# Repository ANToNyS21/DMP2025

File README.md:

# DMP2025
sestava na ONSHAPE : https://cad.onshape.com/documents/a55f27827d7d0bf78ad17041/w/e62290534607ad3c1cca5b53/e/726e90d26969cd6e7ac2d84b?renderMode=0&uiState=67c0b942ae4f594e00a113b2

video s funkčností / ukázkou menu:

https://drive.google.com/file/d/1NYgzzBReGRTbW6AwwNUOp2N6VFr0sSx1/view?usp=sharing

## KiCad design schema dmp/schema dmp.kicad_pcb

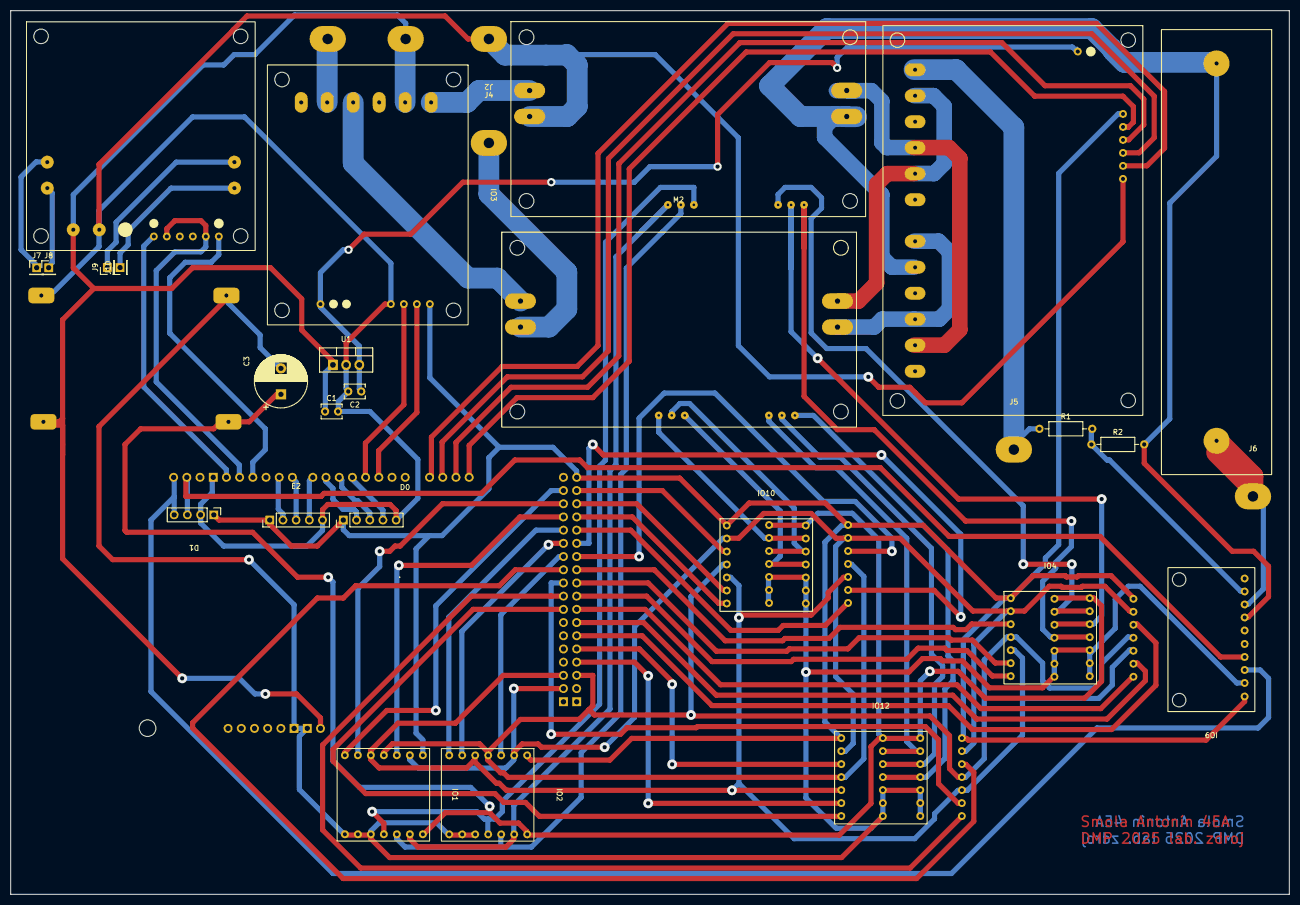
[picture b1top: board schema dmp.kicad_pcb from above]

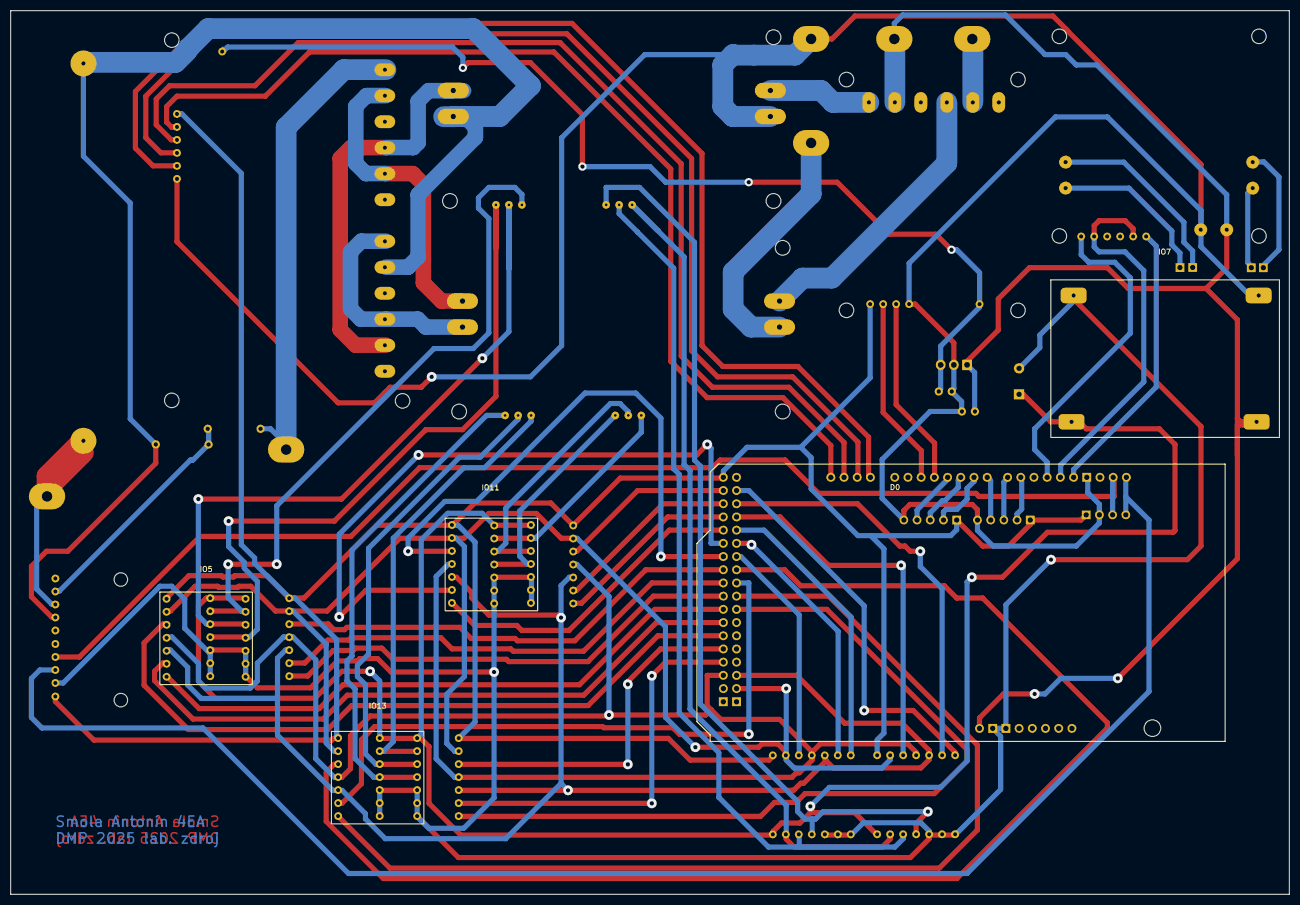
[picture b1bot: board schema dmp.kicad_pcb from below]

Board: 2 copper layers, 246.0 x 170.0 mm, 36 parts (4 on the bottom side), 77 nets.

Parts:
A1: Arduino_Mega2560_R3_Shield; arduino_mega
C1: 0,1 µF; C_Disc_D3.8mm_W2.6mm_P2.50mm
C2: 0,01 µF; C_Disc_D3.8mm_W2.6mm_P2.50mm
C3: 680uF/50V; CP_Radial_D10.0mm_P5.00mm
D1: display
E1: enkoder U; enkoder
E2: enkoder I; enkoder
IO1, IO2, IO10, IO11: MCP41HV51-502E; MCP41HV51
IO3: rele_2x
IO4, IO5, IO12, IO13: MCP41HV51-104E; MCP41HV51
IO7: step_up; step_up_module
IO8: rele_4x
IO9: ADS1115_I2C; ADS1115
IO14: H_mustek
J1: +12v; conn
J2: GND; conn
J3: +12v 2; conn
J4: GND2; conn
J5: out+ regulated; conn
J6: out-; conn
J7: FAN1+; PinHeader_1x01_P2.54mm_Vertical
J8: FAN1-; PinHeader_1x01_P2.54mm_Vertical
J9: FAN2+; PinHeader_1x01_P2.54mm_Vertical
J10: FAN2-; PinHeader_1x01_P2.54mm_Vertical
M1, M2: CC_&_CV_modul
R1: 220k; R_Axial_DIN0207_L6.3mm_D2.5mm_P10.16mm_Horizontal
R2: 17k8; R_Axial_DIN0207_L6.3mm_D2.5mm_P10.16mm_Horizontal
R3: 0.2R; power_rezistor_100w_0.2R
U1: L78S05CV; TO-220-3_Vertical

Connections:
12V+: A1.VIN, C1.1, IO3.22, IO7.1 (VC_+12V), IO14.5 (+12v), J1.1, U1.1 (IN)
+30V digipot: C3.1, IO1.14 (V+30v), IO2.14 (V+30v), IO4.14 (V+30v), IO5.14 (V+30v), IO7.3 (U_OUT), IO10.14 (V+30v), IO11.14 (V+30v), IO12.14 (V+30v), IO13.14 (V+30v)
Arduino_EnA: A1.D13, IO14.7 (ENA)
Arduino_EnB: A1.D11, IO14.8 (ENB)
Arduino_IN2_IN4: A1.D12, IO14.9 (IN1), IO14.12 (IN4)
Arduino_SCL: A1.SCL, D1.4 (SCL), IO9.3 (SCL)
Arduino_SDA: A1.SDA, D1.3 (SDA), IO9.4 (SDA)
Arduino_rele_2x_1: A1.D3 (D3_INT1), IO3.14 (IN1)
Arduino_rele_2x_2: A1.D2 (D2_INT0), IO3.24 (IN2)
Arduino_rele_4x_1: A1.D14 (D14/TX3), IO8.14 (IN1)
Arduino_rele_4x_2: A1.D15 (D15/RX3), IO8.24 (IN2)
Arduino_rele_4x_3: A1.D16 (D16/TX2), IO8.34 (IN3)
Arduino_rele_4x_4: A1.D17 (D17/RX2), IO8.44 (IN4)
CC1: IO10.13 (P0A), IO11.13 (P0A), M2.5 (TRIMR_CC_1)
CC2: IO10.12 (P0W), IO11.12 (P0W), M2.6 (TRIMR_CC_2)
CC3: IO10.11 (P0B), IO11.11 (P0B), M2.7 (TRIMR_CC_3)
CV1: IO12.13 (P0A), IO13.13 (P0A), M2.8 (TRIMR_CV_1)
CV2: IO12.12 (P0W), IO13.12 (P0W), M2.9 (TRIMR_CV_2)
CV3: IO12.11 (P0B), IO13.11 (P0B), M2.10 (TRIMR_CV_3)
GNDD: A1.GND1 (GND), C1.2, C2.2, D1.2 (VCC), E1.5 (GND), E2.5 (GND), IO3.1 (GND), IO7.2 (GND_IN), IO8.1 (GND), IO14.6 (GND), J2.1, M1.2 (IN_GNDD), U1.2 (GND)
JD-VCC: C2.1, IO3.3 (JD-VCC), IO8.3 (JD-VCC), U1.3 (OUT)
MISO_SDO: A1.D50 (D50_MISO), IO1.5 (SDO), IO2.5 (SDO), IO4.5 (SDO), IO5.5 (SDO), IO10.5 (SDO), IO11.5 (SDO), IO12.5 (SDO), IO13.5 (SDO)
MOSI_SDI: A1.D51 (D51_MOSI), IO1.4 (SDI), IO2.4 (SDI), IO4.4 (SDI), IO5.4 (SDI), IO10.4 (SDI), IO11.4 (SDI), IO12.4 (SDI), IO13.4 (SDI)
unnamed: IO1.13 (P0A), IO2.13 (P0A), M1.5 (TRIMR_CC_1)
unnamed: IO1.11 (P0B), IO2.11 (P0B), M1.7 (TRIMR_CC_3)
unnamed: IO1.12 (P0W), IO2.12 (P0W), M1.6 (TRIMR_CC_2)
unnamed: IO4.13 (P0A), IO5.13 (P0A), M1.8 (TRIMR_CV_1)
unnamed: IO4.11 (P0B), IO5.11 (P0B), M1.10 (TRIMR_CV_3)
unnamed: IO4.12 (P0W), IO5.12 (P0W), M1.9 (TRIMR_CV_2)
unnamed: IO8.22, IO9.7 (A0), M1.4 (OUT_GNDD), R2.2, R3.1
unnamed: IO9.8 (A1), J6.1, R3.2
unnamed: IO9.9 (A2), R1.2, R2.1
unnamed: IO14.1 (OUT1), J7.1
unnamed: IO14.2 (OUT2), J8.1
unnamed: IO14.3 (OUT3), J10.1
unnamed: IO14.4 (OUT4), J9.1
unnamed: IO3.12, J3.1
unnamed: J4.1, M2.2 (IN_GNDD)
unnamed: IO8.43, J5.1, R1.1
unnamed: IO3.23, M1.1 (IN_DC_0-30V)
unnamed: IO8.12, IO8.33, M1.3 (OUT_DC_0-30V)
unnamed: IO3.13, M2.1 (IN_DC_0-30V)
unnamed: IO8.32, IO8.42, M2.3 (OUT_DC_0-30V)
unnamed: IO8.13, IO8.23, M2.4 (OUT_GNDD)
arduino 5v: A1.5V4 (5V), D1.1 (GND), E1.1 (5V), E2.1 (5V), IO1.1 (VL_+5v), IO2.1 (VL_+5v), IO3.2 (VCC), IO4.1 (VL_+5v), IO5.1 (VL_+5v), IO8.2 (VCC), IO9.1 (VDD), IO10.1 (VL_+5v), IO11.1 (VL_+5v), IO12.1 (VL_+5v), IO13.1 (VL_+5v)
arduino GND3: A1.GND2 (GND), A1.GND3 (GND), C3.2, IO1.8 (NC), IO1.9 (DGND), IO1.10 (V-), IO2.8 (NC), IO2.9 (DGND), IO2.10 (V-), IO4.8 (NC), IO4.9 (DGND), IO4.10 (V-), IO5.8 (NC), IO5.9 (DGND), IO5.10 (V-), IO7.4 (GND_OUT), IO9.2 (GND), IO10.8 (NC), IO10.9 (DGND), IO10.10 (V-), IO11.8 (NC), IO11.9 (DGND), IO11.10 (V-), IO12.8 (NC), IO12.9 (DGND), IO12.10 (V-), IO13.8 (NC), IO13.9 (DGND), IO13.10 (V-)
arduino sck: A1.D52 (D52_SCK), IO1.2 (SCK), IO2.2 (SCK), IO4.2 (SCK), IO5.2 (SCK), IO10.2 (SCK), IO11.2 (SCK), IO12.2 (SCK), IO13.2 (SCK)
arduino_CS_1: A1.D26, IO1.3 (CS)
arduino_CS_2: A1.D32, IO2.3 (CS)
arduino_CS_3: A1.D35, IO4.3 (CS)
arduino_CS_4: A1.D45, IO5.3 (CS)
arduino_CS_5: A1.D23, IO10.3 (CS)
arduino_CS_6: A1.D33, IO11.3 (CS)
arduino_CS_7: A1.D47, IO12.3 (CS)
arduino_CS_8: A1.D34, IO13.3 (CS)
arduino_SHDN_1: A1.D22, IO1.7 (SHDN)
arduino_SHDN_2: A1.D28, IO2.7 (SHDN)
arduino_SHDN_3: A1.D39, IO4.7 (SHDN)
arduino_SHDN_4: A1.D41, IO5.7 (SHDN)
arduino_SHDN_5: A1.D27, IO10.7 (SHDN)
arduino_SHDN_6: A1.D29, IO11.7 (SHDN)
arduino_SHDN_7: A1.D40, IO12.7 (SHDN)
arduino_SHDN_8: A1.D38, IO13.7 (SHDN)
arduino_WLAT_1: A1.D24, IO1.6 (WLAT)
arduino_WLAT_2: A1.D30, IO2.6 (WLAT)
arduino_WLAT_3: A1.D37, IO4.6 (WLAT)
arduino_WLAT_4: A1.D43, IO5.6 (WLAT)
arduino_WLAT_5: A1.D25, IO10.6 (WLAT)
arduino_WLAT_6: A1.D31, IO11.6 (WLAT)
arduino_WLAT_7: A1.D49, IO12.6 (WLAT)
arduino_WLAT_8: A1.D36, IO13.6 (WLAT)
enkoder I KEY: A1.D9, E2.2 (KEY)
enkoder I S1: A1.D7, E2.4 (S1)
enkoder I S2: A1.D8, E2.3 (S2)
enkoder U KEY: A1.D6, E1.2 (KEY)
enkoder U S1: A1.D4, E1.4 (S1)
enkoder U S2: A1.D5, E1.3 (S2)

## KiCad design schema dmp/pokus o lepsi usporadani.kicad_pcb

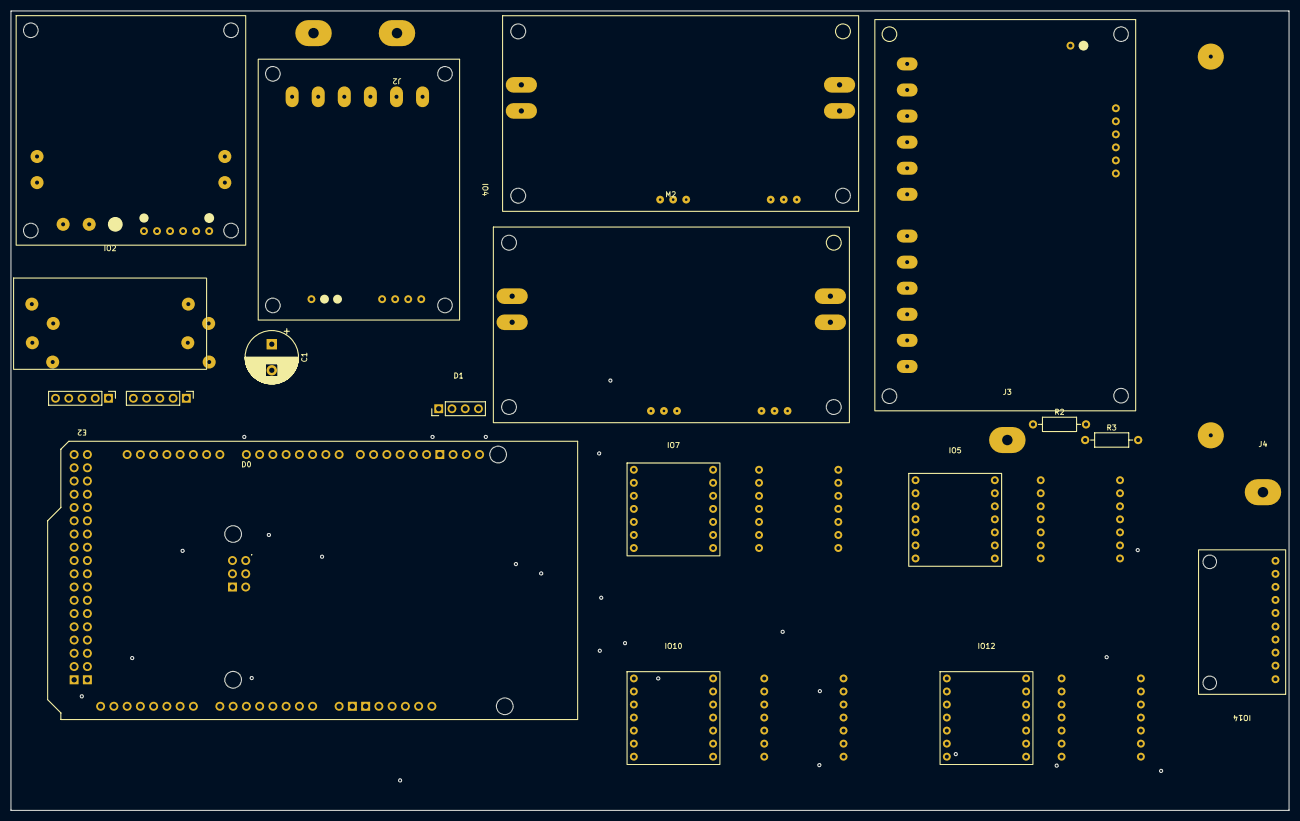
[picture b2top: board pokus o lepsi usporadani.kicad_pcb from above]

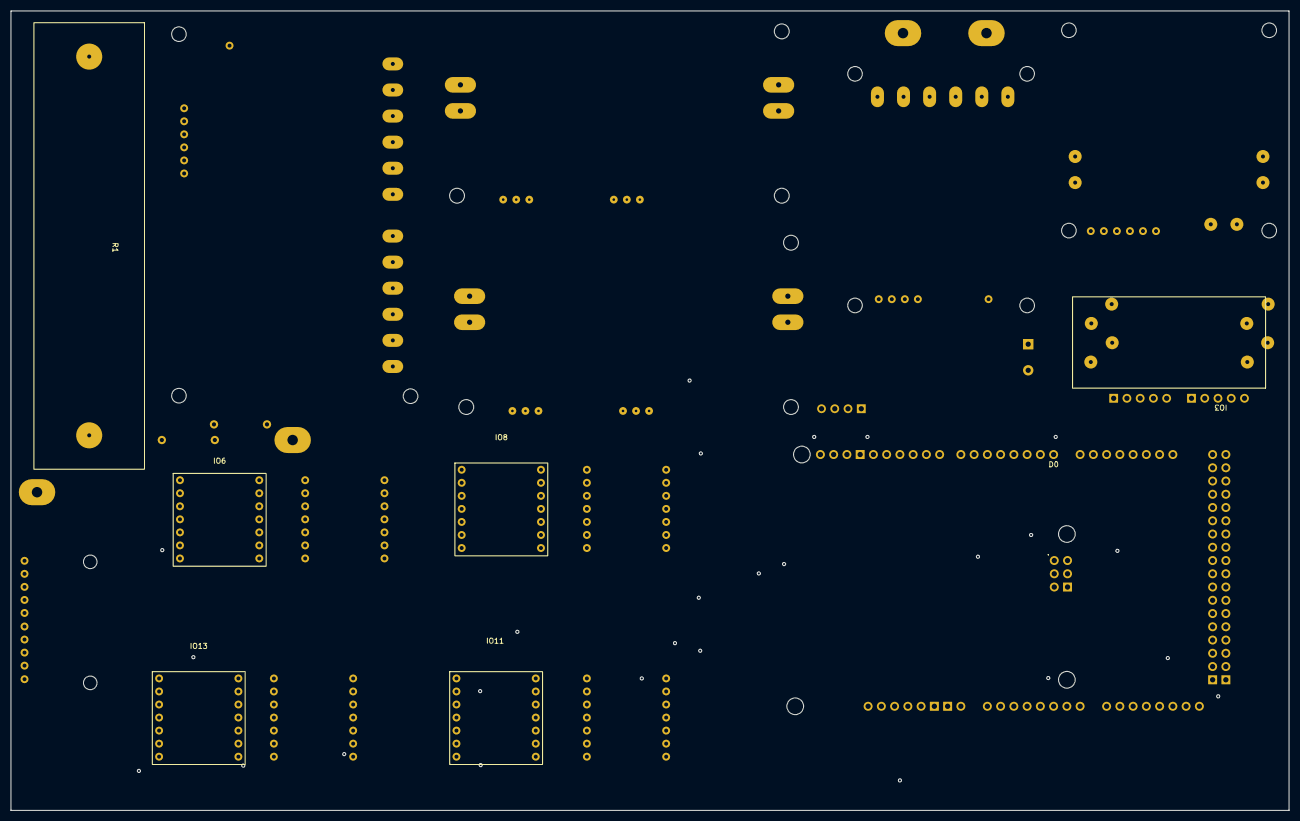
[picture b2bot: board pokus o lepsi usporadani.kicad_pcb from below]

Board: 2 copper layers, 245.0 x 153.2 mm, 28 parts (7 on the bottom side), 71 nets, no tracks yet.

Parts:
A1: Arduino_Mega2560_R3_Shield; arduino_mega
C1: 680uF/50V; CP_Radial_D10.0mm_P5.00mm
D1: display
E1: enkoder U; enkoder
E2: enkoder I; enkoder
IO1: H_mustek
IO2, IO3: step_up_28V
IO4: rele_2x
IO5, IO6, IO10, IO11: MCP41HV51-104E; MCP41HV51
IO7, IO8, IO12, IO13: MCP41HV51-502E; MCP41HV51
IO9: rele_4x
IO14: ADS1115_I2C; ADS1115
J1: +12v; conn
J2: GND; conn
J3: out+ regulated; conn
J4: out-; conn
M1, M2: CC_&_CV_modul
R1: 0.2R; power_rezistor_100w_0.2R
R2: 220k; R_Axial_DIN0207_L6.3mm_D2.5mm_P10.16mm_Horizontal
R3: 17k8; R_Axial_DIN0207_L6.3mm_D2.5mm_P10.16mm_Horizontal

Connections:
12V+: IO1.5 (+12v), IO2.1 (VC_+12V), IO3.1 (VC_+12V), IO4.12, IO4.22, J1.1
+30V digipot: C1.1, IO2.3 (28V_OUT), IO5.14 (V+30v), IO6.14 (V+30v), IO7.14 (V+30v), IO8.14 (V+30v), IO10.14 (V+30v), IO11.14 (V+30v), IO12.14 (V+30v), IO13.14 (V+30v)
Arduino_EnA: A1.D8, IO1.7 (ENA)
Arduino_IN1: A1.D9, IO1.9 (IN1)
Arduino_IN2: A1.D10, IO1.10 (IN2)
Arduino_SCL: A1.SCL, D1.4 (SCL), IO14.4 (SDA)
Arduino_SDA: A1.SDA, D1.3 (SDA), IO14.3 (SCL)
Arduino_rele_2x_1: A1.D2 (D2_INT0), IO4.14 (IN1)
Arduino_rele_2x_2: A1.D3 (D3_INT1), IO4.24 (IN2)
Arduino_rele_4x_1: A1.D4, IO9.14 (IN1)
Arduino_rele_4x_2: A1.D5, IO9.24 (IN2)
Arduino_rele_4x_3: A1.D6, IO9.34 (IN3)
Arduino_rele_4x_4: A1.D7, IO9.44 (IN4)
GNDD: A1.GND1 (GND), D1.2 (VCC), E1.5 (GND), E2.5 (GND), IO1.6 (GND), IO2.2 (GND_IN), IO3.2 (GND_IN), IO4.1 (GND), IO9.1 (GND), J2.1, M1.2 (IN_GNDD), M2.2 (IN_GNDD)
MISO_SDO: A1.D50 (D50_MISO), IO5.5 (SDO), IO6.5 (SDO), IO7.5 (SDO), IO8.5 (SDO), IO10.5 (SDO), IO11.5 (SDO), IO12.5 (SDO), IO13.5 (SDO)
MOSI_SDI: A1.D51 (D51_MOSI), IO5.4 (SDI), IO6.4 (SDI), IO7.4 (SDI), IO8.4 (SDI), IO10.4 (SDI), IO11.4 (SDI), IO12.4 (SDI), IO13.4 (SDI)
unnamed: A1.D24, E1.2 (KEY)
unnamed: A1.D23, E1.4 (S1)
unnamed: A1.D22, E1.3 (S2)
unnamed: A1.D27, E2.2 (KEY)
unnamed: A1.D26, E2.4 (S1)
unnamed: A1.D25, E2.3 (S2)
unnamed: IO2.4 (GND_OUT), IO3.3 (28V_OUT)
unnamed: IO5.13 (P0A), IO6.13 (P0A), M1.10 (TRIMR_CV_3)
unnamed: IO5.11 (P0B), IO6.11 (P0B), M1.8 (TRIMR_CV_1)
unnamed: IO5.12 (P0W), IO6.12 (P0W), M1.9 (TRIMR_CV_2)
unnamed: IO7.13 (P0A), IO8.13 (P0A), M1.5 (TRIMR_CC_1)
unnamed: IO7.11 (P0B), IO8.11 (P0B), M1.7 (TRIMR_CC_3)
unnamed: IO7.12 (P0W), IO8.12 (P0W), M1.6 (TRIMR_CC_2)
unnamed: IO10.13 (P0A), IO11.13 (P0A), M2.10 (TRIMR_CV_3)
unnamed: IO10.11 (P0B), IO11.11 (P0B), M2.8 (TRIMR_CV_1)
unnamed: IO10.12 (P0W), IO11.12 (P0W), M2.9 (TRIMR_CV_2)
unnamed: IO12.13 (P0A), IO13.13 (P0A), M2.5 (TRIMR_CC_1)
unnamed: IO12.11 (P0B), IO13.11 (P0B), M2.7 (TRIMR_CC_3)
unnamed: IO12.12 (P0W), IO13.12 (P0W), M2.6 (TRIMR_CC_2)
unnamed: IO9.22, IO14.7 (A0), M1.4 (OUT_GNDD), R1.1, R3.2
unnamed: IO14.8 (A1), J4.1, R1.2
unnamed: IO14.9 (A2), R2.2, R3.1
unnamed: IO9.43, J3.1, R2.1
unnamed: IO4.23, M1.1 (IN_DC_0-30V)
unnamed: IO9.12, IO9.33, M1.3 (OUT_DC_0-30V)
unnamed: IO4.13, M2.1 (IN_DC_0-30V)
unnamed: IO9.32, IO9.42, M2.3 (OUT_DC_0-30V)
unnamed: IO9.13, IO9.23, M2.4 (OUT_GNDD)
arduino 5v: A1.5V4 (5V), D1.1 (GND), E1.1 (5V), E2.1 (5V), IO4.2 (VCC), IO5.1 (VL_+5v), IO6.1 (VL_+5v), IO7.1 (VL_+5v), IO8.1 (VL_+5v), IO9.2 (VCC), IO10.1 (VL_+5v), IO11.1 (VL_+5v), IO12.1 (VL_+5v), IO13.1 (VL_+5v), IO14.1 (VDD)
arduino GND3: A1.GND2 (GND), A1.GND3 (GND), C1.2, IO3.4 (GND_OUT), IO5.8 (NC), IO5.9 (DGND), IO5.10 (V-), IO6.8 (NC), IO6.9 (DGND), IO6.10 (V-), IO7.8 (NC), IO7.9 (DGND), IO7.10 (V-), IO8.8 (NC), IO8.9 (DGND), IO8.10 (V-), IO10.8 (NC), IO10.9 (DGND), IO10.10 (V-), IO11.8 (NC), IO11.9 (DGND), IO11.10 (V-), IO12.8 (NC), IO12.9 (DGND), IO12.10 (V-), IO13.8 (NC), IO13.9 (DGND), IO13.10 (V-), IO14.2 (GND)
arduino sck: A1.D52 (D52_SCK), IO5.2 (SCK), IO6.2 (SCK), IO7.2 (SCK), IO8.2 (SCK), IO10.2 (SCK), IO11.2 (SCK), IO12.2 (SCK), IO13.2 (SCK)
arduino_CS_1: A1.D19 (D19/RX1), IO7.3 (CS)
arduino_CS_2: A1.D16 (D16/TX2), IO8.3 (CS)
arduino_CS_3: A1.D11, IO5.3 (CS)
arduino_CS_4: A1.D28, IO6.3 (CS)
arduino_CS_5: A1.D31, IO12.3 (CS)
arduino_CS_6: A1.D34, IO13.3 (CS)
arduino_CS_7: A1.D37, IO10.3 (CS)
arduino_CS_8: A1.D40, IO11.3 (CS)
arduino_SHDN_1: A1.D17 (D17/RX2), IO7.7 (SHDN)
arduino_SHDN_2: A1.D14 (D14/TX3), IO8.7 (SHDN)
arduino_SHDN_3: A1.D13, IO5.7 (SHDN)
arduino_SHDN_4: A1.D30, IO6.7 (SHDN)
arduino_SHDN_5: A1.D33, IO12.7 (SHDN)
arduino_SHDN_6: A1.D36, IO13.7 (SHDN)
arduino_SHDN_7: A1.D39, IO10.7 (SHDN)
arduino_SHDN_8: A1.D42, IO11.7 (SHDN)
arduino_WLAT_1: A1.D18 (D18/TX1), IO7.6 (WLAT)
arduino_WLAT_2: A1.D15 (D15/RX3), IO8.6 (WLAT)
arduino_WLAT_3: A1.D12, IO5.6 (WLAT)
arduino_WLAT_4: A1.D29, IO6.6 (WLAT)
arduino_WLAT_5: A1.D32, IO12.6 (WLAT)
arduino_WLAT_6: A1.D35, IO13.6 (WLAT)
arduino_WLAT_7: A1.D38, IO10.6 (WLAT)
arduino_WLAT_8: A1.D41, IO11.6 (WLAT)

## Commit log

2025-02-05 kicad libraries
2025-02-05 added some files
2025-02-12 textova cast
2025-02-19 pridani check hodnot pred a po zapsani do DCP
2025-02-21 added dps doc
2025-02-22 changes to documentation
2025-02-22 added photos and dir
2025-02-24 added actual usage and it is working
2025-02-25 added all zadani
2025-02-25 added corection to voltage and maybe soved the dcp not found issue
2025-02-25 file edit
2025-02-25 added 3d files
2025-02-25 failed
2025-02-25 VRKSJL
2025-02-25 failed add
2025-02-25 added measured current compensation
2025-02-25 added out cur correction
2025-02-25 added program tings
2025-02-26 finalni zakrytovani
2025-02-26 added el files
2025-02-27 make curent measurement more acurate
2025-02-27 final version
2025-02-27 file managemant
2025-02-28 files
2025-02-28 fotos
2025-02-28 documetation
2025-04-01 bordel removal
